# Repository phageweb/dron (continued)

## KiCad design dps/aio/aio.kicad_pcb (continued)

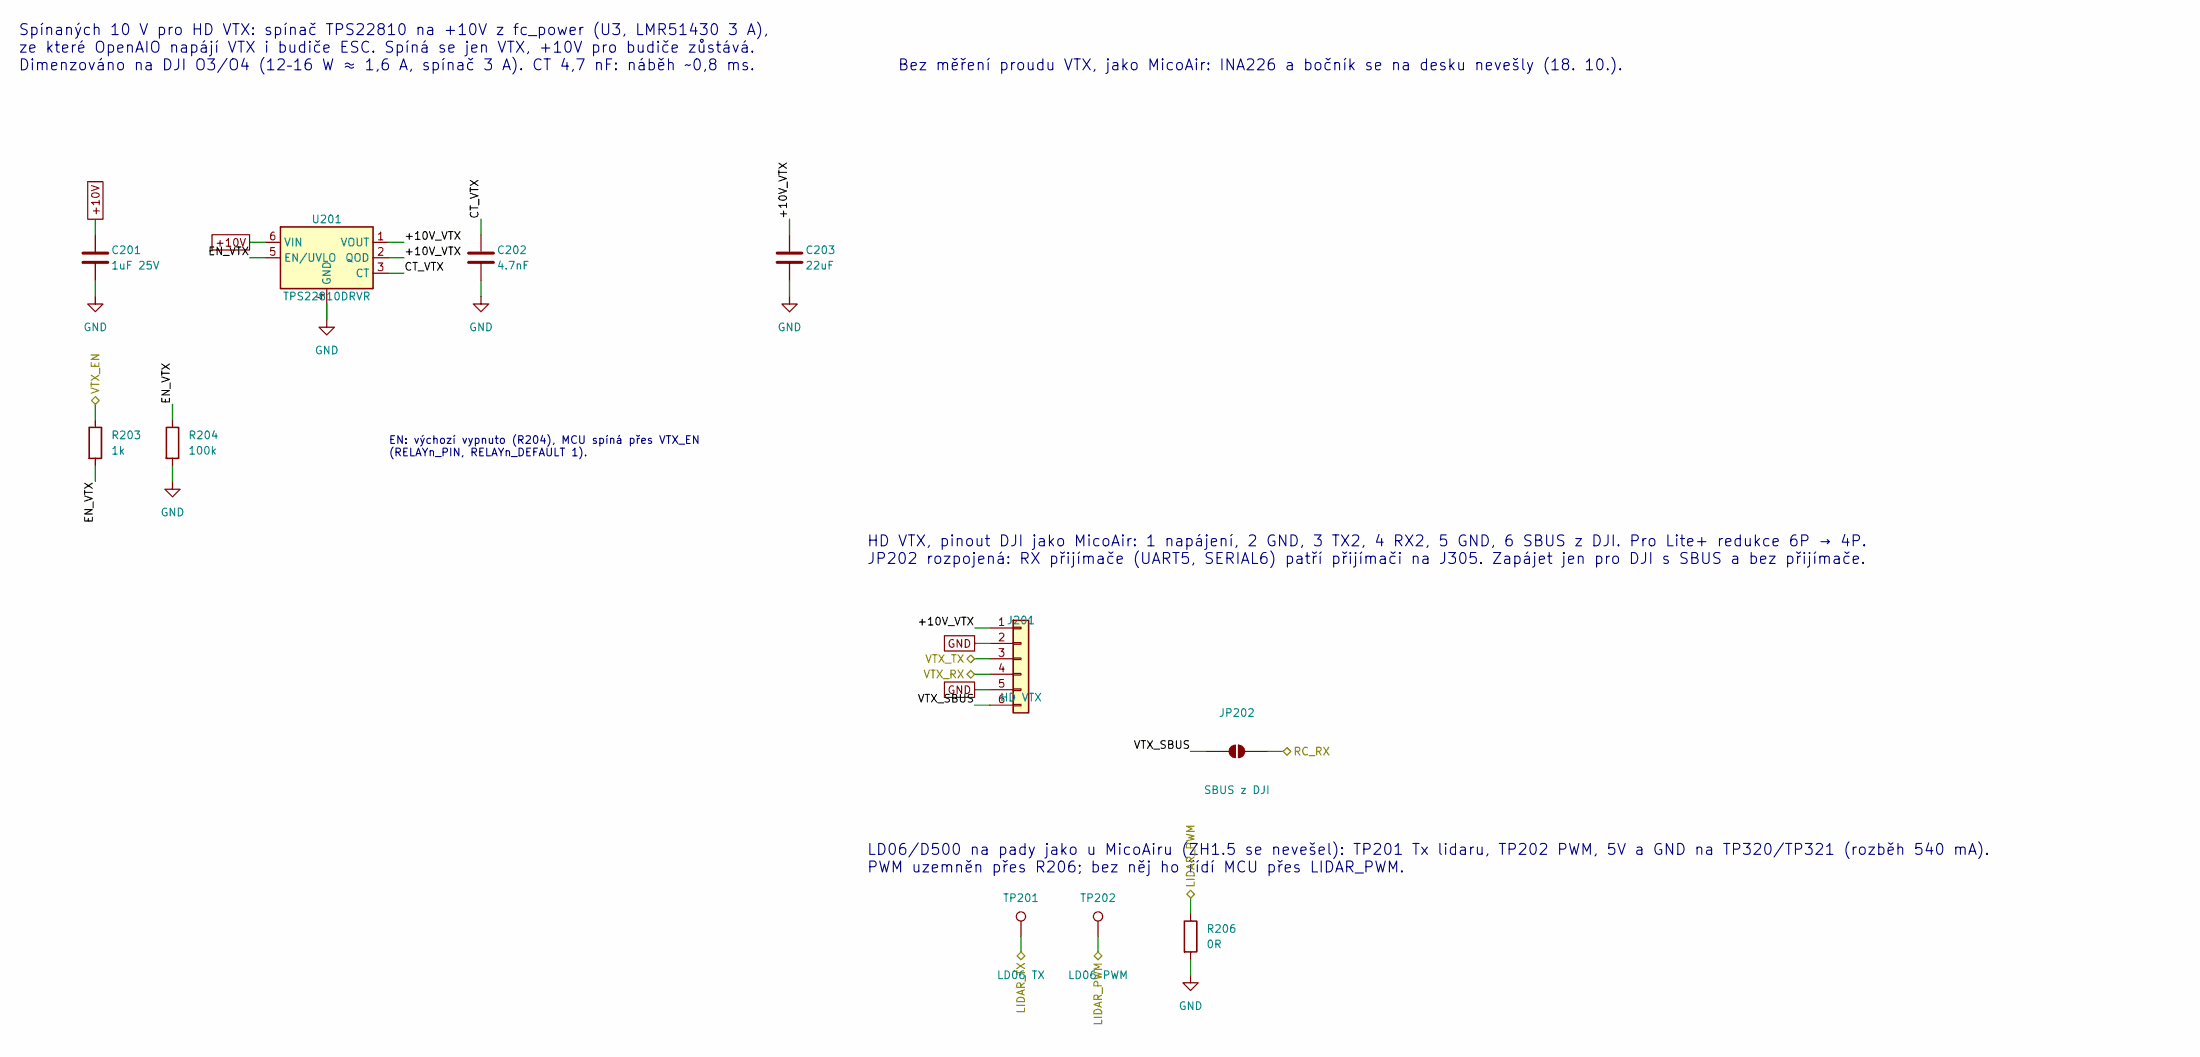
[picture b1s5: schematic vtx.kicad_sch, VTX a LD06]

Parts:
C201: 1uF 25V; C_0402_1005Metric
C202: 4.7nF; C_0201_0603Metric
C203: 22uF; C_0603_1608Metric; LCSC C2762594
J201: HD VTX; JST_SH_SM06B-SRSS-TB_1x06-1MP_P1.00mm_Horizontal; LCSC C160405
JP202: SBUS z DJI; SolderJumper-2_P1.3mm_Open_Pad1.0x1.5mm
R203: 1k; R_0201_0603Metric
R204: 100k; R_0201_0603Metric; LCSC C270364
R206: 0R; R_0201_0603Metric
TP201: LD06 TX; Pad_1.0x1.4mm
TP202: LD06 PWM; Pad_1.0x1.4mm
U201: TPS22810DRVR; WSON-6-1EP_2x2mm_P0.65mm_EP1x1.6mm

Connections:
+10V: C201.1, U201.6 (VIN); also elsewhere on the board
/LIDAR_PWM: R206.1, TP202.1; also elsewhere on the board
/LIDAR_TX: TP201.1; also elsewhere on the board
/RC_RX: JP202.2 (B); also elsewhere on the board
/VTX a LD06/+10V_VTX: C203.1, J201.1, U201.1 (VOUT), U201.2 (QOD)
/VTX a LD06/CT_VTX: C202.1, U201.3 (CT)
/VTX a LD06/EN_VTX: R203.2, R204.1, U201.5 (EN/UVLO)
/VTX a LD06/VTX_SBUS: J201.6, JP202.1 (A)
/VTX_EN: R203.1; also elsewhere on the board
/VTX_RX: J201.4; also elsewhere on the board
/VTX_TX: J201.3; also elsewhere on the board
GND: C201.2, C202.2, C203.2, J201.2, J201.5, R204.2, R206.2, U201.4 (GND), U201.7 (GND); also elsewhere on the board

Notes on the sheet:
Spínaných 10 V pro HD VTX: spínač TPS22810 na +10V z fc_power (U3, LMR51430 3 A), ze které OpenAIO napájí VTX i budiče ESC. Spíná se jen VTX, +10V pro budiče zůstává. Dimenzováno na DJI O3/O4 (12–16 W ≈ 1,6 A, spínač 3 A). CT 4,7 nF: náběh ~0,8 ms.
EN: výchozí vypnuto (R204), MCU spíná přes VTX_EN (RELAYn_PIN, RELAYn_DEFAULT 1).
Bez měření proudu VTX, jako MicoAir: INA226 a bočník se na desku nevešly (18. 10.).
HD VTX, pinout DJI jako MicoAir: 1 napájení, 2 GND, 3 TX2, 4 RX2, 5 GND, 6 SBUS z DJI. Pro Lite+ redukce 6P → 4P. JP202 rozpojená: RX přijímače (UART5, SERIAL6) patří přijímači na J305. Zapájet jen pro DJI s SBUS a bez přijímače.
LD06/D500 na pady jako u MicoAiru (ZH1.5 se nevešel): TP201 Tx lidaru, TP202 PWM, 5V a GND na TP320/TP321 (rozběh 540 mA). PWM uzemněn přes R206; bez něj ho řídí MCU přes LIDAR_PWM.

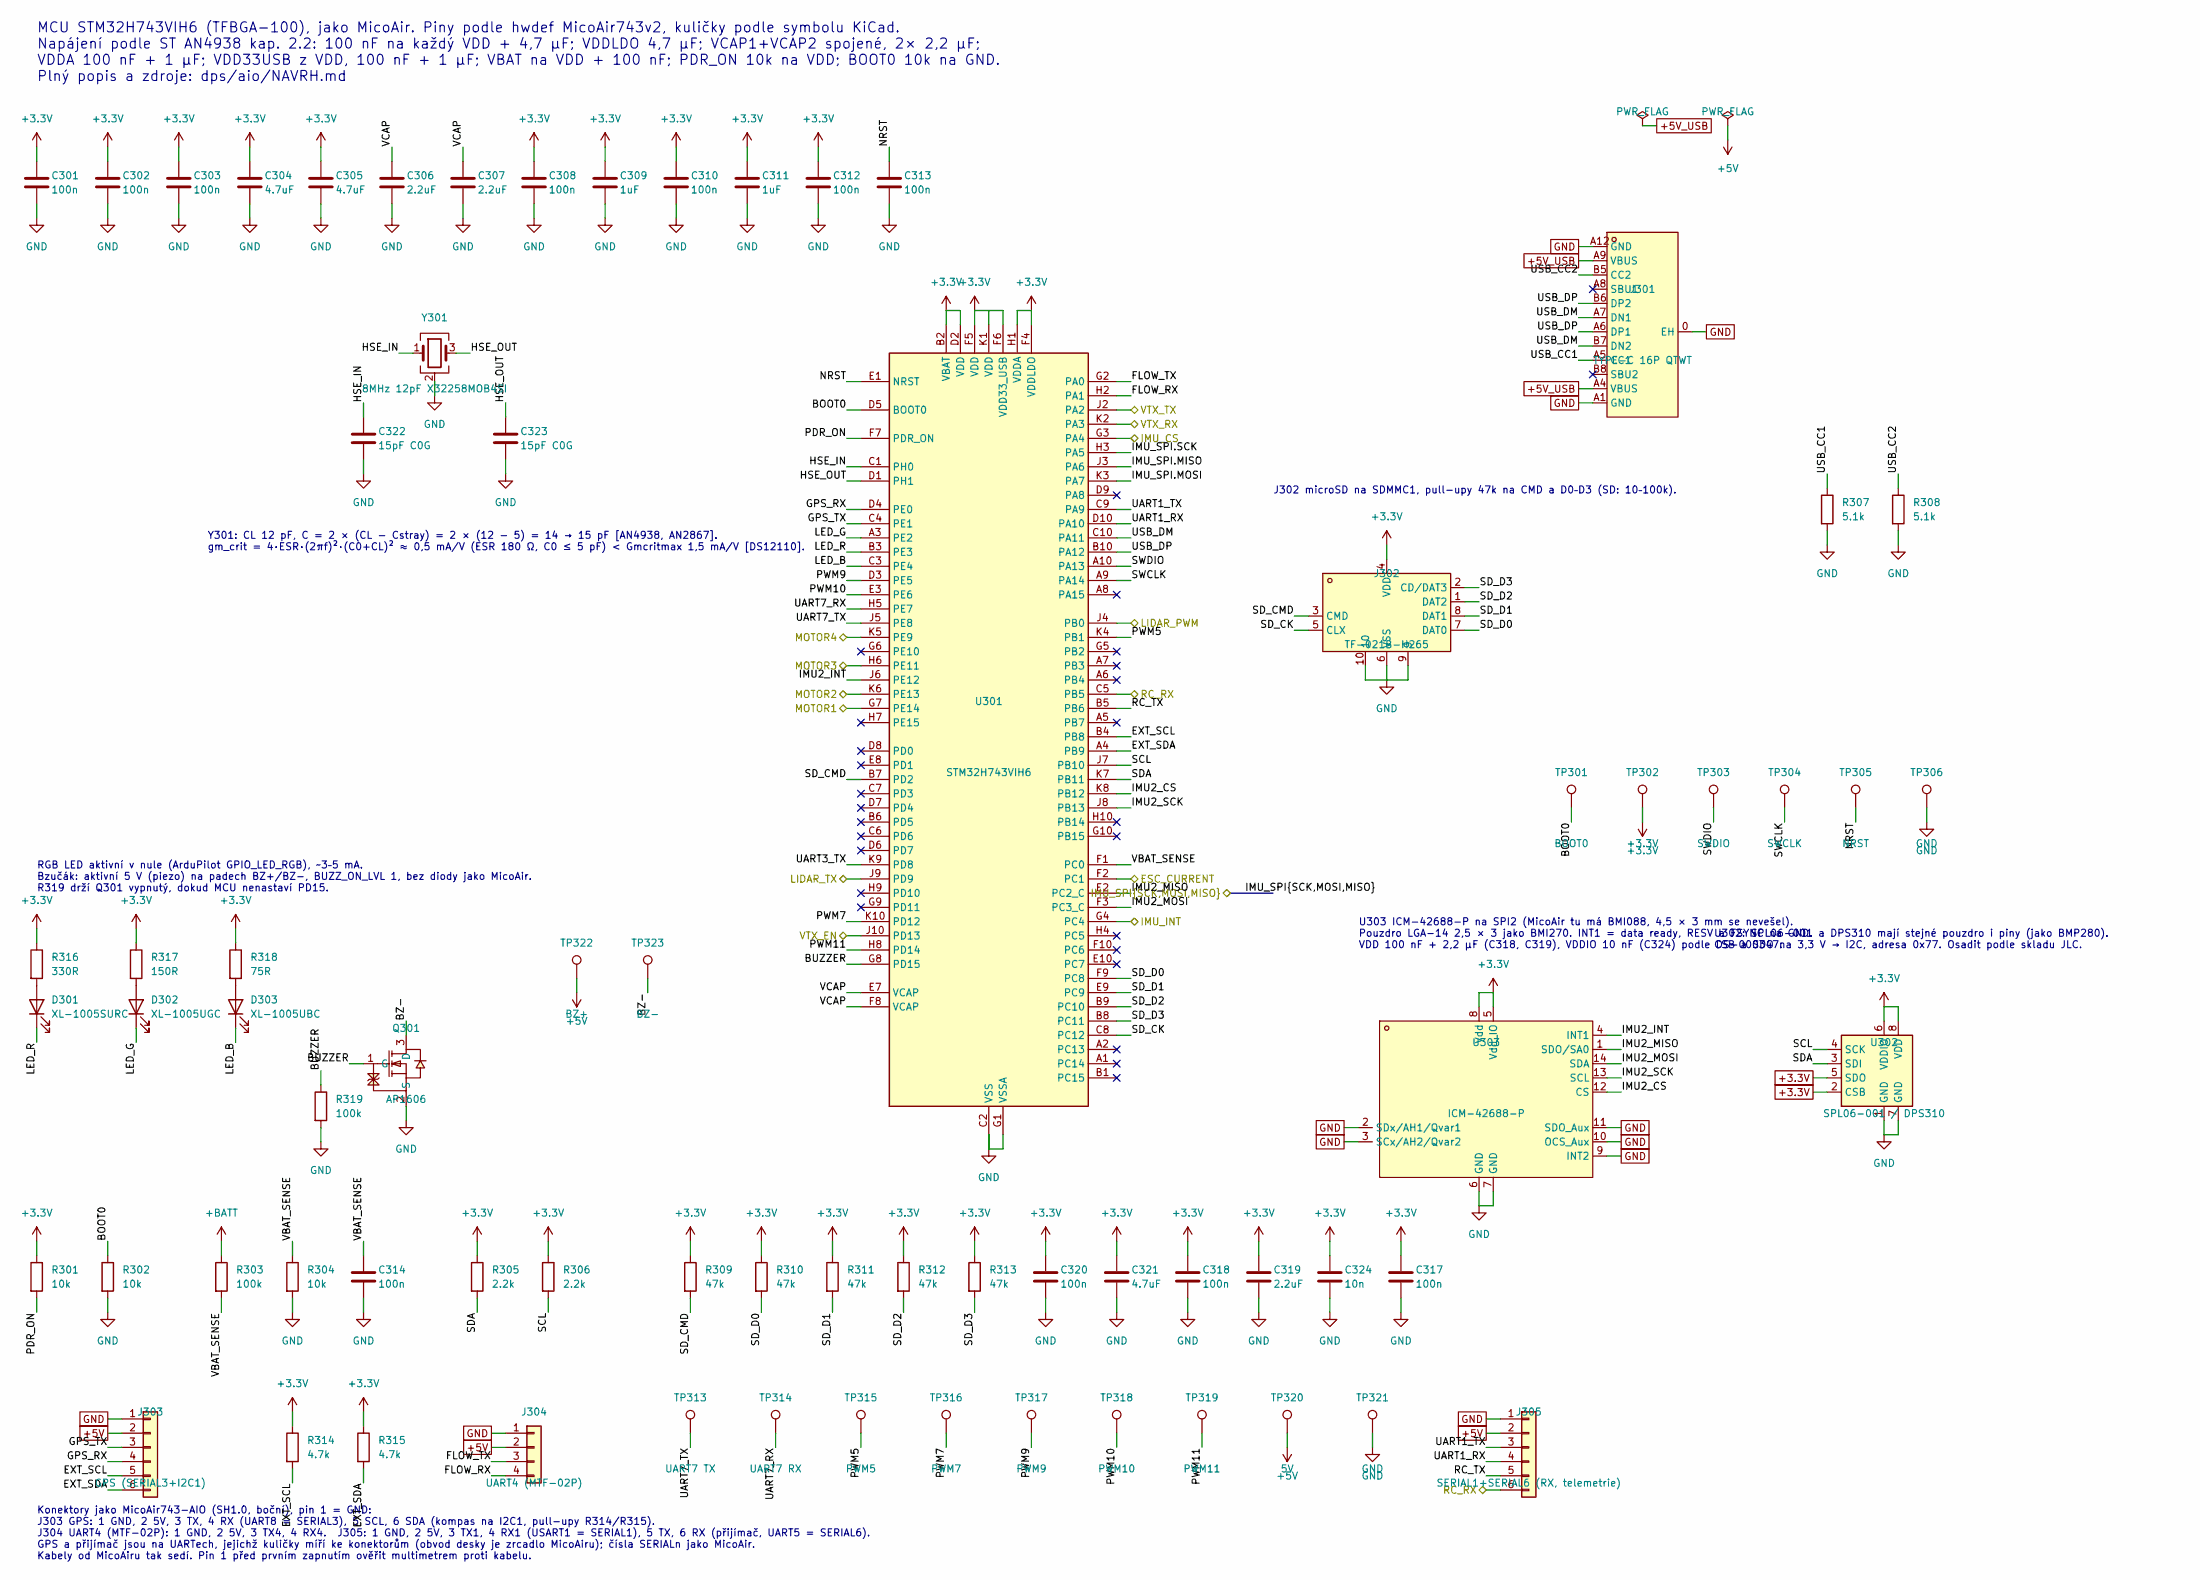
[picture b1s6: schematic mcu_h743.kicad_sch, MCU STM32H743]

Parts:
C301, C302, C303, C308, C310, C312, C313, C314, C317, C318, C320: 100n; C_0201_0603Metric; LCSC C76939
C304, C305, C321: 4.7uF; C_0402_1005Metric; LCSC C23733
C306, C307: 2.2uF; C_0402_1005Metric
C309, C311: 1uF; C_0402_1005Metric
C319: 2.2uF; C_0201_0603Metric
C322, C323: 15pF C0G; C_0402_1005Metric
C324: 10n; C_0201_0603Metric
D301: XL-1005SURC; LED_0402_1005Metric; LCSC C965790
D302: XL-1005UGC; LED_0402_1005Metric; LCSC C965793
D303: XL-1005UBC; LED_0402_1005Metric; LCSC C22355736
J301: TYPE-C 16P QTWT; USB-TYPE-C-SMD_TYPE-C-16P-QTWT; LCSC C5187472
J302: TF-021B-H265; TF-SMD_TF-021B-H265; LCSC C498185
J303: GPS (SERIAL3+I2C1); JST_SH_SM06B-SRSS-TB_1x06-1MP_P1.00mm_Horizontal; LCSC C160405
J304: UART4 (MTF-02P); JST_SH_SM04B-SRSS-TB_1x04-1MP_P1.00mm_Horizontal
J305: SERIAL1+SERIAL6 (RX, telemetrie); JST_SH_SM06B-SRSS-TB_1x06-1MP_P1.00mm_Horizontal; LCSC C160405
Q301: AP1606; DFN-3L_L1.0-W0.6-P0.65-BR; LCSC C2849580
R301, R302, R304: 10k; R_0201_0603Metric
R303, R319: 100k; R_0201_0603Metric; LCSC C270364
R305, R306: 2.2k; R_0201_0603Metric
R307, R308: 5.1k; R_0201_0603Metric; LCSC C270344
R309, R310, R311, R312, R313: 47k; R_0201_0603Metric
R314, R315: 4.7k; R_0201_0603Metric
R316: 330R; R_0201_0603Metric
R317: 150R; R_0201_0603Metric
R318: 75R; R_0201_0603Metric
TP301: BOOT0; Pad_1.0x1.4mm
TP302: +3.3V; Pad_1.0x1.4mm
TP303: SWDIO; Pad_1.0x1.4mm
TP304: SWCLK; Pad_1.0x1.4mm
TP305: NRST; Pad_1.0x1.4mm
TP306, TP321: GND; Pad_1.0x1.4mm
TP313: UART7 TX; Pad_1.0x1.4mm
TP314: UART7 RX; Pad_1.0x1.4mm
TP315: PWM5; Pad_1.0x1.4mm
TP316: PWM7; Pad_1.0x1.4mm
TP317: PWM9; Pad_1.0x1.4mm
TP318: PWM10; Pad_1.0x1.4mm
TP319: PWM11; Pad_1.0x1.4mm
TP320: 5V; Pad_1.0x1.4mm
TP322: BZ+; Pad_1.0x1.4mm
TP323: BZ-; Pad_1.0x1.4mm
U301: STM32H743VIH6; TFBGA-100_8x8mm_Layout10x10_P0.8mm
U302: SPL06-001 / DPS310; Bosch_LGA-8_2x2.5mm_P0.65mm_ClockwisePinNumbering; LCSC C2684428
U303: ICM-42688-P; LGA-14_L3.0-W2.5-P0.50-BR
Y301: 8MHz 12pF X32258MOB4SI; Crystal_SMD_3225-4Pin_3.2x2.5mm; LCSC C2682775

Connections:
+3.3V: C301.1, C302.1, C303.1, C304.1, C305.1, C308.1, C309.1, C310.1, C311.1, C312.1, C317.1, C318.1, C319.1, C320.1, C321.1, C324.1, J302.4 (VDD), R301.1, R305.1, R306.1, R309.1, R310.1, R311.1, R312.1, R313.1, R314.1, R315.1, R316.1, R317.1, R318.1, TP302.1, U301.B2 (VBAT), U301.D2 (VDD), U301.F4 (VDDLDO), U301.F5 (VDD), U301.F6 (VDD33_USB), U301.H1 (VDDA), U301.K1 (VDD), U302.2 (CSB), U302.5 (SDO), U302.6 (VDDIO), U302.8 (VDD), U303.5 (Vdd_IO), U303.8 (Vdd); also elsewhere on the board
+5V: J303.2, J304.2, J305.2, TP320.1, TP322.1; also elsewhere on the board
+5V_USB: J301.A4 (VBUS), J301.A9 (VBUS); also elsewhere on the board
+BATT: R303.1; also elsewhere on the board
/ESC_CURRENT: U301.F2 (PC1); also elsewhere on the board
/IMU_CS: U301.G3 (PA4); also elsewhere on the board
/IMU_INT: U301.G4 (PC4); also elsewhere on the board
/IMU_SPI.MISO: U301.J3 (PA6); also elsewhere on the board
/IMU_SPI.MOSI: U301.K3 (PA7); also elsewhere on the board
/IMU_SPI.SCK: U301.H3 (PA5); also elsewhere on the board
/LIDAR_PWM: U301.J4 (PB0); also elsewhere on the board
/LIDAR_TX: U301.J9 (PD9); also elsewhere on the board
/MCU H743/BOOT0: R302.1, TP301.1, U301.D5 (BOOT0)
/MCU H743/BUZZER: Q301.1 (G), R319.1, U301.G8 (PD15)
/MCU H743/BZ-: Q301.3 (D), TP323.1
/MCU H743/EXT_SCL: J303.5, R314.2, U301.B4 (PB8)
/MCU H743/EXT_SDA: J303.6, R315.2, U301.A4 (PB9)
/MCU H743/FLOW_RX: J304.4, U301.H2 (PA1)
/MCU H743/FLOW_TX: J304.3, U301.G2 (PA0)
/MCU H743/GPS_RX: J303.4, U301.D4 (PE0)
/MCU H743/GPS_TX: J303.3, U301.C4 (PE1)
/MCU H743/HSE_IN: C322.1, U301.C1 (PH0), Y301.1
/MCU H743/HSE_OUT: C323.1, U301.D1 (PH1), Y301.3
/MCU H743/IMU2_CS: U301.K8 (PB12), U303.12 (CS)
/MCU H743/IMU2_INT: U301.J6 (PE12), U303.4 (INT1)
/MCU H743/IMU2_MISO: U301.E2 (PC2_C), U303.1 (SDO/SA0)
/MCU H743/IMU2_MOSI: U301.F3 (PC3_C), U303.14 (SDA)
/MCU H743/IMU2_SCK: U301.J8 (PB13), U303.13 (SCL)
/MCU H743/LED_B: D303.1 (K), U301.C3 (PE4)
/MCU H743/LED_G: D302.1 (K), U301.A3 (PE2)
/MCU H743/LED_R: D301.1 (K), U301.B3 (PE3)
/MCU H743/NRST: C313.1, TP305.1, U301.E1 (NRST)
/MCU H743/PDR_ON: R301.2, U301.F7 (PDR_ON)
/MCU H743/PWM5: TP315.1, U301.K4 (PB1)
/MCU H743/PWM7: TP316.1, U301.K10 (PD12)
/MCU H743/PWM9: TP317.1, U301.D3 (PE5)
/MCU H743/PWM10: TP318.1, U301.E3 (PE6)
/MCU H743/PWM11: TP319.1, U301.H8 (PD14)
/MCU H743/RC_TX: J305.5, U301.B5 (PB6)
/MCU H743/SCL: R306.2, U301.J7 (PB10), U302.4 (SCK)
/MCU H743/SDA: R305.2, U301.K7 (PB11), U302.3 (SDI)
/MCU H743/SD_CK: J302.5 (CLX), U301.C8 (PC12)
/MCU H743/SD_CMD: J302.3 (CMD), R309.2, U301.B7 (PD2)
/MCU H743/SD_D0: J302.7 (DAT0), R310.2, U301.F9 (PC8)
/MCU H743/SD_D1: J302.8 (DAT1), R311.2, U301.E9 (PC9)
/MCU H743/SD_D2: J302.1 (DAT2), R312.2, U301.B9 (PC10)
/MCU H743/SD_D3: J302.2 (CD/DAT3), R313.2, U301.B8 (PC11)
/MCU H743/SWCLK: TP304.1, U301.A9 (PA14)
/MCU H743/SWDIO: TP303.1, U301.A10 (PA13)
/MCU H743/UART1_RX: J305.4, U301.D10 (PA10)
/MCU H743/UART1_TX: J305.3, U301.C9 (PA9)
/MCU H743/UART3_TX: U301.K9 (PD8)
/MCU H743/UART7_RX: TP314.1, U301.H5 (PE7)
/MCU H743/UART7_TX: TP313.1, U301.J5 (PE8)
/MCU H743/USB_CC1: J301.A5 (CC1), R307.1
/MCU H743/USB_CC2: J301.B5 (CC2), R308.1
/MCU H743/USB_DM: J301.A7 (DN1), J301.B7 (DN2), U301.C10 (PA11)
/MCU H743/USB_DP: J301.A6 (DP1), J301.B6 (DP2), U301.B10 (PA12)
/MCU H743/VBAT_SENSE: C314.1, R303.2, R304.1, U301.F1 (PC0)
/MCU H743/VCAP: C306.1, C307.1, U301.E7 (VCAP), U301.F8 (VCAP)
/MOTOR1: U301.G7 (PE14); also elsewhere on the board
/MOTOR2: U301.K6 (PE13); also elsewhere on the board
/MOTOR3: U301.H6 (PE11); also elsewhere on the board
/MOTOR4: U301.K5 (PE9); also elsewhere on the board
/RC_RX: J305.6, U301.C5 (PB5); also elsewhere on the board
/VTX_EN: U301.J10 (PD13); also elsewhere on the board
/VTX_RX: U301.K2 (PA3); also elsewhere on the board
/VTX_TX: U301.J2 (PA2); also elsewhere on the board
GND: C301.2, C302.2, C303.2, C304.2, C305.2, C306.2, C307.2, C308.2, C309.2, C310.2, C311.2, C312.2, C313.2, C314.2, C317.2, C318.2, C319.2, C320.2, C321.2, C322.2, C323.2, C324.2, J301.0 (EH), J301.A1 (GND), J301.A12 (GND), J302.6 (VSS), J302.9, J302.10, J303.1, J304.1, J305.1, Q301.2 (S), R302.2, R304.2, R307.2, R308.2, R319.2, TP306.1, TP321.1, U301.C2 (VSS), U301.E4 (VSS), U301.E5 (VSS), U301.E6 (VSS), U301.G1 (VSSA), U301.J1 (VSS), U302.1 (GND), U302.7 (GND), U303.2 (SDx/AH1/Qvar1), U303.3 (SCx/AH2/Qvar2), U303.6 (GND), U303.7 (GND), U303.9 (INT2), U303.10 (OCS_Aux), U303.11 (SDO_Aux), Y301.2 (G), Y301.4 (G); also elsewhere on the board
unnamed: D301.2 (A), R316.2
unnamed: D302.2 (A), R317.2
unnamed: D303.2 (A), R318.2

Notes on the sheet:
MCU STM32H743VIH6 (TFBGA-100), jako MicoAir. Piny podle hwdef MicoAir743v2, kuličky podle symbolu KiCad. Napájení podle ST AN4938 kap. 2.2: 100 nF na každý VDD + 4,7 µF; VDDLDO 4,7 µF; VCAP1+VCAP2 spojené, 2× 2,2 µF; VDDA 100 nF + 1 µF; VDD33USB z VDD, 100 nF + 1 µF; VBAT na VDD + 100 nF; PDR_ON 10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
RGB LED aktivní v nule (ArduPilot GPIO_LED_RGB), ~3–5 mA. Bzučák: aktivní 5 V (piezo) na padech BZ+/BZ−, BUZZ_ON_LVL 1, bez diody jako MicoAir. R319 drží Q301 vypnutý, dokud MCU nenastaví PD15.
Y301: CL 12 pF, C = 2 × (CL − Cstray) = 2 × (12 − 5) = 14 → 15 pF [AN4938, AN2867]. gm_crit = 4·ESR·(2πf)²·(C0+CL)² ≈ 0,5 mA/V (ESR 180 Ω, C0 ≤ 5 pF) < Gmcritmax 1,5 mA/V [DS12110].
U302: SPL06-001 a DPS310 mají stejné pouzdro i piny (jako BMP280). CSB a SDO na 3,3 V → I2C, adresa 0x77. Osadit podle skladu JLC.
U303 ICM-42688-P na SPI2 (MicoAir tu má BMI088, 4,5 × 3 mm se nevešel). Pouzdro LGA-14 2,5 × 3 jako BMI270. INT1 = data ready, RESV a FSYNC na GND. VDD 100 nF + 2,2 µF (C318, C319), VDDIO 10 nF (C324) podle DS-000347.
J302 microSD na SDMMC1, pull-upy 47k na CMD a D0–D3 (SD: 10–100k).
Konektory jako MicoAir743-AIO (SH1.0, boční), pin 1 = GND: J303 GPS: 1 GND, 2 5V, 3 TX, 4 RX (UART8 = SERIAL3), 5 SCL, 6 SDA (kompas na I2C1, pull-upy R314/R315). J304 UART4 (MTF-02P): 1 GND, 2 5V, 3 TX4, 4 RX4. J305: 1 GND, 2 5V, 3 TX1, 4 RX1 (USART1 = SERIAL1), 5 TX, 6 RX (přijímač, UART5 = SERIA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

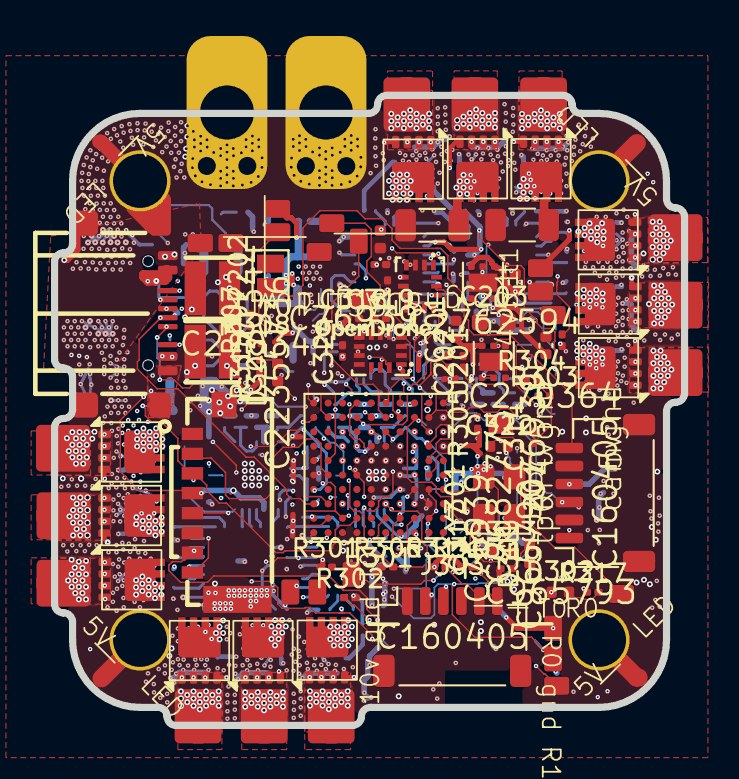
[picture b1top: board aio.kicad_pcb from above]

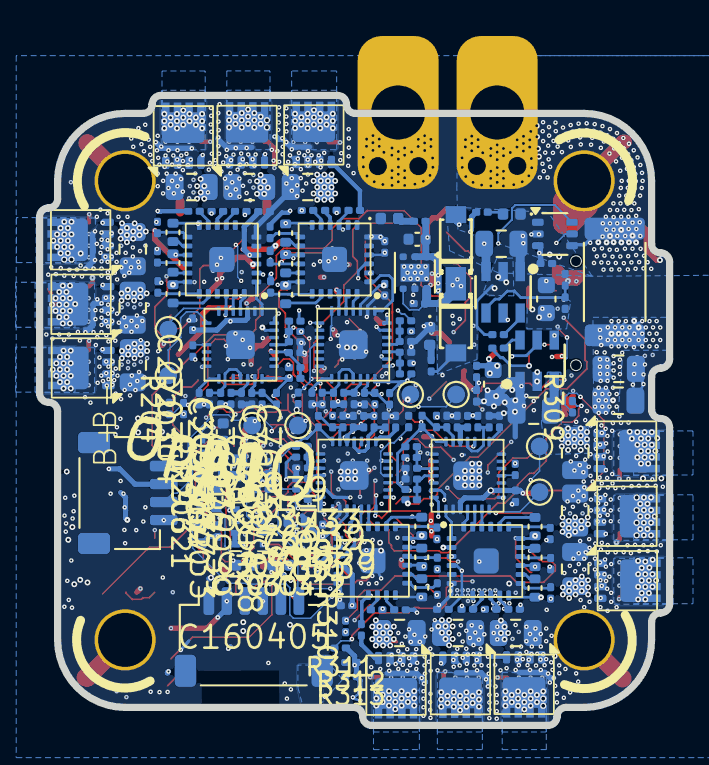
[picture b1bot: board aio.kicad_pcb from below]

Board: 8 copper layers, 35.0 x 35.0 mm, 280 parts (200 on the bottom side), 225 nets.

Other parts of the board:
R54, R74: 15R; R_0201_0603Metric
R59: 10R; R_0201_0603Metric
R76: 10k; R_0201_0603Metric

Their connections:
+3.3V: R59.2; also elsewhere on the board
/ESC2/GHA: R54.1; also elsewhere on the board
/ESC2/vdda: R59.1; also elsewhere on the board
/ESC3/GLA: R74.1; also elsewhere on the board
GND: R76.2; also elsewhere on the board
unnamed 171: R54.2; also elsewhere on the board
unnamed 178: R74.2; also elsewhere on the board
unnamed 211: R76.1; also elsewhere on the board

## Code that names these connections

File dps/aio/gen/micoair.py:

"""MicoAir743v2-AIO-45A reference; deliberately not the older 35 A AIO.

Pinout: https://micoair.com/flightcontroller_micoair743v2_aio_45a/
Firmware: external/ardupilot/.../hwdef/MicoAir743v2/hwdef.dat (pinned locally).
This is a functional reference, not a reconstruction of its undocumented copper.
"""
import re

# Logical board signal -> MCU GPIO. ICM42688 takes the BMI088 accelerometer's
# SPI2 CS/DRDY; this is our adaptation, not a claim about MicoAir's fitted IMU.
PINS = {
    "MOTOR1": "PE14", "MOTOR2": "PE13", "MOTOR3": "PE11", "MOTOR4": "PE9",
    "IMU_SPI.SCK": "PB3", "IMU_SPI.MISO": "PB4", "IMU_SPI.MOSI": "PD6",
    "IMU_CS": "PA15", "IMU_INT": "PB7",
    "IMU2_SCK": "PD3", "IMU2_MISO": "PC2", "IMU2_MOSI": "PC3",
    "IMU2_CS": "PD4", "IMU2_INT": "PC14",
    "GPS_TX": "PD8", "GPS_RX": "PD9", "RC_TX": "PC6", "RC_RX": "PC7",
    "LIDAR_TX": "PB5", "UART5_TX": "PB6", "UART8_TX": "PE1", "UART8_RX": "PE0",
    "UART1_TX": "PA9", "UART1_RX": "PA10", "VTX_TX": "PA2", "VTX_RX": "PA3",
    "FLOW_TX": "PA0", "FLOW_RX": "PA1", "EXT_SCL": "PB8", "EXT_SDA": "PB9",
    "SCL": "PB10", "SDA": "PB11", "VBAT_SENSE": "PC0", "ESC_CURRENT": "PC1",
    "USB_DM": "PA11", "USB_DP": "PA12", "SWDIO": "PA13", "SWCLK": "PA14",
    "SD_CK": "PC12", "SD_CMD": "PD2", "SD_D0": "PC8", "SD_D1": "PC9",
    "SD_D2": "PC10", "SD_D3": "PC11", "LED_R": "PE3", "LED_G": "PE2", "LED_B": "PE4",
    "BUZZER": "PD15", "PWM5": "PB1", "LIDAR_PWM": "PB0", "PWM7": "PD12",
    "VTX_EN": "PD13", "PWM9": "PE5", "PWM10": "PE6", "PWM11": "PD14",
}
ALIASES = {"UART3_TX": "UART5_TX", "UART7_TX": "UART8_TX", "UART7_RX": "UART8_RX"}
SERIAL_ORDER = "OTG1 USART1 USART2 USART3 UART4 UART5 USART6 UART7 UART8"


def gpio(name):
    """KiCad calls the analog-switch pins PC2_C/PC3_C; hwdef calls them PC2/PC3."""
    match = re.match(r"P[A-K]\d+", name)
    return match.group() if match else name


def remap(balls, pin_names):
    by_pin = {gpio(name): ball for ball, name in pin_names.items()}
    out = {ball: net for ball, net in balls.items() if ALIASES.get(net, net) not in PINS}
    for net, pin in PINS.items():
        ball = by_pin[pin]
        if ball in out and out[ball] is not None:
            raise ValueError(f"{net}/{pin} would replace {out[ball]} at {ball}")
        out[ball] = net
    return out


def hwdef(text):
    """Render the reference variant from our board's hwdef, keeping its electrical calibration."""
    text = re.sub(r"SERIAL_ORDER[^\n]*", "SERIAL_ORDER  " + SERIAL_ORDER, text)
    start, end = text.index("# order of UARTs"), text.index("# SWD")
    uarts = "\n".join(f"{pin:4} {bus}_{direction:2} {bus}" for bus, tx, rx in (
        ("USART1", "PA9", "PA10"), ("USART2", "PA2", "PA3"), ("USART3", "PD8", "PD9"),
        ("UART4", "PA0", "PA1"), ("UART5", "PB6", "PB5"), ("USART6", "PC6", "PC7"),
        ("UART7", "PE8", "PE7"), ("UART8", "PE1", "PE0"))
        for pin, direction in ((tx, "TX"), (rx, "RX")))
    text = text[:start] + ("# UART order/pins follow MicoAir743v2-AIO-45A.\n"
        "# SERIAL3 GPS; SERIAL5 LD06; SERIAL6 RC; SERIAL8 Bluetooth pads.\n"
        "SERIAL_ORDER  " + SERIAL_ORDER + "\n\nPA11 OTG_FS_DM OTG1\nPA12 OTG_FS_DP OTG1\n\n"
        + uarts + "\n\n") + text[end:]
    start, end = text.index("# SPI2 -"), text.index("# IMUs:")
    text = text[:start] + """# SPI2: our ICM42688 on the reference BMI088 accel CS/DRDY pins.
PD3 SPI2_SCK SPI2
PC2 SPI2_MISO SPI2
PC3 SPI2_MOSI SPI2
PD4 ICM42688_CS CS
PC14 DRDY1_ICM42688 INPUT

# SPI3: BMI270, same pins as MicoAir743v2-AIO-45A.
PB3 SPI3_SCK SPI3
PB4 SPI3_MISO SPI3
PD6 SPI3_MOSI SPI3
PA15 BMI270_CS CS
PB7 DRDY3_BMI270 INPUT

SPIDEV icm42688 SPI2 DEVID1 ICM42688_CS MODE3 2*MHZ 16*MHZ
SPIDEV bmi270 SPI3 DEVID1 BMI270_CS MODE3 1*MHZ 10*MHZ

""" + text[end:]
    return "# Generated reference variant by gen/micoair.py; verify IMU rotations after placement.\n" + text

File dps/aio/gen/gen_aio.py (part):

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v.part("JP202", "Jumper:SolderJumper_2_Open", "SBUS z DJI", "Jumper:SolderJumper-2_P1.3mm_Open_Pad1.0x1.5mm", "",
       238.76, 132.08, {"1": "VTX_SBUS", "2": "RC_RX"})
v.text("Spínaných 10 V pro HD VTX: spínač TPS22810 na +10V z fc_power (U3, LMR51430 3 A),\nze které OpenAIO napájí VTX i budiče ESC. Spíná se jen VTX, +10V pro budiče zůstává.\nDimenzováno na DJI O3/O4 (12–16 W ≈ 1,6 A, spínač 3 A). CT 4,7 nF: náběh ~0,8 ms.", 38.1, 20.32, 1.8)
v.text("EN: výchozí vypnuto (R204), MCU spíná přes VTX_EN\n(RELAYn_PIN, RELAYn_DEFAULT 1).", 99.06, 83.82)
v.text("Bez měření proudu VTX, jako MicoAir: INA226 a bočník se na desku nevešly (18. 10.).", 182.88, 20.32, 1.8)
v.text("HD VTX, pinout DJI jako MicoAir: 1 napájení, 2 GND, 3 TX2, 4 RX2, 5 GND, 6 SBUS z DJI. Pro Lite+ redukce 6P → 4P.\nJP202 rozpojená: RX přijímače (UART5, SERIAL6) patří přijímači na J305. Zapájet jen pro DJI s SBUS a bez přijímače.", 177.8, 101.6, 1.8)
v.text("LD06/D500 na pady jako u MicoAiru (ZH1.5 se nevešel): TP201 Tx lidaru, TP202 PWM, 5V a GND na TP320/TP321 (rozběh 540 mA).\nPWM uzemněn přes R206; bez něj ho řídí MCU přes LIDAR_PWM.", 177.8, 152.4, 1.8)
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    "C1": "HSE_IN", "D1": "HSE_OUT",
    # hwdef MicoAir743v2, except three UARTs (19. 10.): our board's edge is MicoAir's mirrored, so GPS and the
    # receiver take the UARTs whose balls face the connectors (bottom edge); SERIAL_ORDER keeps MicoAir's numbers
    "G7": "MOTOR1", "K6": "MOTOR2", "H6": "MOTOR3", "K5": "MOTOR4",            # PE14 PE13 PE11 PE9, TIM1
    # both IMUs sit above the BGA (19. 10.): BMI270 on SPI1 (free, MicoAir's OSD) instead of SPI3, whose
    # balls face down; the ICM's SCK, CS and DRDY on balls of the top rows
    "H3": "IMU_SPI.SCK", "K3": "IMU_SPI.MOSI", "J3": "IMU_SPI.MISO",           # PA5 PA7 PA6, SPI1
    "G3": "IMU_CS", "G4": "IMU_INT",                                          # PA4 PC4, BMI270
    "J8": "IMU2_SCK", "E2": "IMU2_MISO", "F3": "IMU2_MOSI",                   # PB13 PC2_C PC3_C, SPI2
    "K8": "IMU2_CS", "J6": "IMU2_INT",                                       # PB12 PE12, ICM-42688-P
    "F1": "VBAT_SENSE", "F2": "ESC_CURRENT",                                  # PC0 PC1, ADC1
    "K7": "SDA", "J7": "SCL",                                                 # PB11 PB10, I2C2 = bus 0
    "A4": "EXT_SDA", "B4": "EXT_SCL",                                         # PB9 PB8, I2C1 = bus 1
    "C9": "UART1_TX", "D10": "UART1_RX",                                      # PA9 PA10, SERIAL1
    "J2": "VTX_TX", "K2": "VTX_RX",                                           # PA2 PA3, USART2 = SERIAL2
    "C4": "GPS_TX", "D4": "GPS_RX",                                           # PE1 PE0, UART8 = SERIAL3
    "G2": "FLOW_TX", "H2": "FLOW_RX",                                         # PA0 PA1, UART4 = SERIAL4
    "K9": "UART3_TX", "J9": "LIDAR_TX",                                       # PD8 PD9, USART3 = SERIAL5
    "B5": "RC_TX", "C5": "RC_RX",                                             # PB6 PB5, UART5 = SERIAL6
    "J5": "UART7_TX", "H5": "UART7_RX",                                       # PE8 PE7, SERIAL8
    "C10": "USB_DM", "B10": "USB_DP",                                         # PA11 PA12, OTG_FS
    "A10": "SWDIO", "A9": "SWCLK",                                            # PA13 PA14
    "C8": "SD_CK", "B7": "SD_CMD", "F9": "SD_D0", "E9": "SD_D1", "B9": "SD_D2", "B8": "SD_D3",  # SDMMC1
    "B3": "LED_R", "A3": "LED_G", "C3": "LED_B", "G8": "BUZZER",              # PE3 PE2 PE4 PD15
    "J4": "LIDAR_PWM", "J10": "VTX_EN",                                       # PB0 = PWM6, PD13 = PWM8
    "K4": "PWM5", "K10": "PWM7", "D3": "PWM9", "E3": "PWM10", "H8": "PWM11",  # PB1 PD12 PE5 PE6 PD14
}
_balls = pins_of(LIB["MCU_ST_STM32H7:STM32H743VIHx"])
if MICOAIR:
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m.part("TP323", "lib:TestPoint", "BZ-", TP, "", 139.7, 182.88, {"1": "BZ-"})
m.text("""RGB LED aktivní v nule (ArduPilot GPIO_LED_RGB), ~3–5 mA.
Bzučák: aktivní 5 V (piezo) na padech BZ+/BZ−, BUZZ_ON_LVL 1, bez diody jako MicoAir.
R319 drží Q301 vypnutý, dokud MCU nenastaví PD15.""", 30.48, 167.64, 1.27)
m.text("""Y301: CL 12 pF, C = 2 × (CL − Cstray) = 2 × (12 − 5) = 14 → 15 pF [AN4938, AN2867].
gm_crit = 4·ESR·(2πf)²·(C0+CL)² ≈ 0,5 mA/V (ESR 180 Ω, C0 ≤ 5 pF) < Gmcritmax 1,5 mA/V [DS12110].""", 60.96, 106.68, 1.27)
m.text("""U302: SPL06-001 a DPS310 mají stejné pouzdro i piny (jako BMP280).
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J304 UART4 (MTF-02P): 1 GND, 2 5V, 3 TX4, 4 RX4.  J305: 1 GND, 2 5V, 3 TX1, 4 RX1 (USART1 = SERIAL1), 5 TX, 6 RX (přijímač, UART5 = SERIAL6).
GPS a přijímač jsou na UARTech, jejichž kuličky míří ke konektorům (obvod desky je zrcadlo MicoAiru); čísla SERIALn jako MicoAir.
Kabely od MicoAiru tak sedí. Pin 1 před prvním zapnutím ověřit multimetrem proti kabelu.""" if not MICOAIR else
"""Reference MicoAir743v2-AIO-45A: J303 GPS USART3 (PD8/PD9), J305 RC USART6 (PC6/PC7).
LD06 UART5 RX PB5; Bluetooth UART8 PE1/PE0. BMI270 SPI3, ICM42688 SPI2.
Konektory mají náš pinout; orientaci a pin 1 ověřit proti kabelu. Layout této varianty čeká na ověření.""",
       30.48, 287.02, 1.27)
m.place("#FLG301", "power:PWR_FLAG", "PWR_FLAG", "", "", 317.5, 30.48, power=True, ref_at=(317.5, 27), val_at=(317.5, 27.94))
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
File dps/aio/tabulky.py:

#!/usr/bin/env python3
"""Regenerate the tables in NAVRH.md from the schematic.

    nix develop ./dps -c python3 dps/aio/tabulky.py [PROJECT] [--profile current|micoair-v2]

Exports the netlist with kicad-cli and rewrites everything between the
<!-- tabulky:NAME --> and <!-- /tabulky:NAME --> markers in NAVRH.md.
"""
import argparse, collections, os, re, subprocess, tempfile
import xml.etree.ElementTree as ET

parser = argparse.ArgumentParser(description=__doc__)
parser.add_argument("project", nargs="?", default=os.path.dirname(os.path.abspath(__file__)))
parser.add_argument("--profile", choices=("current", "micoair-v2"), default="current")
args = parser.parse_args()
HERE = os.path.abspath(args.project)
DOC = os.path.join(HERE, "NAVRH.md")

# What each H743 signal does in ArduPilot (hwdef Pavo20AIO: MicoAir743v2, IMUs and three UARTs moved) and where it goes.
FUNCTION = {
    "MOTOR1": "PWM1, TIM1_CH4, BIDIR DShot", "MOTOR2": "PWM2, TIM1_CH3", "MOTOR3": "PWM3, TIM1_CH2, BIDIR DShot",
    "MOTOR4": "PWM4, TIM1_CH1", "PWM5": "PWM5, TIM3_CH4, GPIO 54", "LIDAR_PWM": "PWM6, TIM3_CH3, GPIO 55",
    "PWM7": "PWM7, TIM4_CH1, GPIO 56", "VTX_EN": "PWM8 jako GPIO 57 (RELAYn_PIN 57)", "PWM9": "PWM9, TIM15_CH1, GPIO 58",
    "PWM10": "PWM10, TIM15_CH2, GPIO 59", "PWM11": "PWM11, TIM4_CH3, GPIO 60 (LED pad)",
    "IMU_SPI.SCK": "SPI1_SCK", "IMU_SPI.MOSI": "SPI1_MOSI", "IMU_SPI.MISO": "SPI1_MISO", "IMU_CS": "BMI270_CS",
    "IMU_INT": "DRDY3_BMI270", "IMU2_SCK": "SPI2_SCK", "IMU2_MISO": "SPI2_MISO", "IMU2_MOSI": "SPI2_MOSI",
    "IMU2_CS": "ICM42688_CS", "IMU2_INT": "DRDY1_ICM42688", "VBAT_SENSE": "ADC1 ch10, BATT_VOLTAGE_SENS",
    "ESC_CURRENT": "ADC1 ch11, BATT_CURRENT_SENS", "SDA": "I2C2_SDA (bus 0)", "SCL": "I2C2_SCL (bus 0)",
    "EXT_SDA": "I2C1_SDA (bus 1)", "EXT_SCL": "I2C1_SCL (bus 1)", "UART1_TX": "USART1_TX, SERIAL1",
    "UART1_RX": "USART1_RX, SERIAL1", "VTX_TX": "USART2_TX, SERIAL2", "VTX_RX": "USART2_RX, SERIAL2",
    "GPS_TX": "UART8_TX, SERIAL3", "GPS_RX": "UART8_RX, SERIAL3", "FLOW_TX": "UART4_TX, SERIAL4",
    "FLOW_RX": "UART4_RX, SERIAL4", "UART3_TX": "USART3_TX, SERIAL5", "LIDAR_TX": "USART3_RX, SERIAL5",
    "RC_TX": "UART5_TX, SERIAL6", "RC_RX": "UART5_RX, SERIAL6", "UART7_TX": "UART7_TX, SERIAL8",
    "UART7_RX": "UART7_RX, SERIAL8",
    "USB_DM": "OTG_FS_DM, SERIAL0", "USB_DP": "OTG_FS_DP, SERIAL0", "SWDIO": "SWD", "SWCLK": "SWD",
    "SD_CK": "SDMMC1_CK", "SD_CMD": "SDMMC1_CMD", "SD_D0": "SDMMC1_D0", "SD_D1": "SDMMC1_D1",
    "SD_D2": "SDMMC1_D2", "SD_D3": "SDMMC1_D3", "LED_R": "LED_RED, GPIO 0", "LED_G": "LED_GREEN, GPIO 1",
    "LED_B": "LED_BLUE, GPIO 2", "BUZZER": "BUZZER, GPIO 61", "HSE_IN": "OSC_IN, 8 MHz", "HSE_OUT": "OSC_OUT",
    "BOOT0": "BOOT0", "NRST": "reset", "PDR_ON": "napěťový dozor", "VCAP": "výstup LDO jádra",
}
if args.profile == "micoair-v2":
    FUNCTION.update({
        "IMU_SPI.SCK": "SPI3_SCK", "IMU_SPI.MOSI": "SPI3_MOSI", "IMU_SPI.MISO": "SPI3_MISO",
        "GPS_TX": "USART3_TX, SERIAL3", "GPS_RX": "USART3_RX, SERIAL3",
        "RC_TX": "USART6_TX, SERIAL6", "RC_RX": "USART6_RX, SERIAL6",
        "LIDAR_TX": "UART5_RX, SERIAL5", "UART5_TX": "UART5_TX, SERIAL5",
        "UART8_TX": "UART8_TX, SERIAL8", "UART8_RX": "UART8_RX, SERIAL8",
    })


def netlist():
    with tempfile.TemporaryDirectory() as d:
        out = os.path.join(d, "aio.xml")
        subprocess.run(["kicad-cli", "sch", "export", "netlist", "--format", "kicadxml", "-o", out,
                        os.path.join(HERE, "aio.kicad_sch")], check=True, capture_output=True)
        return ET.parse(out).getroot()


def short(net):
    return re.sub(r"^/(?:[^/]+/)*", "", net) if net.startswith("/") else net


def main():
    t = netlist()
    comps = {}
    for c in t.find("components"):
        f = {x.get("name"): x.text or "" for x in c.findall("fields/field")}
        comps[c.get("ref")] = dict(value=c.findtext("value"), fp=(c.findtext("footprint") or "").split(":")[-1],
                                   lcsc=f.get("LCSC", ""), sheet=c.find("sheetpath").get("names"))
    pins = collections.defaultdict(dict)
    nets = collections.defaultdict(list)
    for n in t.find("nets"):
        name = n.get("name")
        for x in n.findall("node"):
            pins[x.get("ref")][x.get("pin")] = (name, x.get("pinfunction") or "")
            nets[name].append(x.get("ref"))

    tables = {}

    # bill of materials, per sheet
    by = collections.defaultdict(list)
    for ref, c in comps.items():
        by[c["sheet"]].append(ref)
    key = lambda r: (re.sub(r"\d+", "", r), int(re.sub(r"\D", "", r) or 0))
    out = []
    for sheet in sorted(by, key=lambda s: (s != "/", s)):
        refs = sorted(by[sheet], key=key)
        out.append(f"\n**{sheet}** ({len(refs)} dílů)\n")
        out.append("| Ref | Hodnota | Pouzdro | LCSC |")
        out.append("| --- | --- | --- | --- |")
        for r in refs:
            c = comps[r]
            out.append(f"| {r} | {c['value']} | {c['fp']} | {c['lcsc'] or '—'} |")
    tables["kusovnik"] = "\n".join(out)

    # H743 pin map
    out = ["| Kulička | Pin | Síť | Funkce (hwdef Pavo20AIO) | Kam vede |", "| --- | --- | --- | --- | --- |"]
    rows = []
    for ball, (net, func) in pins["U301"].items():
        pin = func.rsplit("_", 1)[0]
        s = short(net)
        if s.startswith("unconnected"):
            s, goes = "—", "nezapojeno"
        else:
            others = sorted({r for r in nets[net] if r != "U301"}, key=key)
            if len(others) > 12:
                goes = f"napájecí síť ({len(others)} dílů)"
            else:
                goes = ", ".join(others) if others else "jen štítek, čeká na zapojení"
        rows.append((pin, ball, s, FUNCTION.get(s, ""), goes))
    order = lambda r: (r[0][:2] if r[0].startswith("P") else "~", int(re.sub(r"\D", "", r[0][2:]) or 0), r[0])
    for pin, ball, s, f, goes in sorted(rows, key=order):
        out.append(f"| {ball} | {pin} | {s} | {f} | {goes} |")
    tables["piny"] = "\n".join(out)

    # nets crossing sheets
    out = ["| Síť | Listy | Součástky |", "| --- | --- | --- |"]
    for name, refs in sorted(nets.items(), key=lambda kv: short(kv[0])):
        sheets = sorted({comps[r]["sheet"] for r in refs})
        if len(sheets) > 1 and short(name) not in ("GND",):
            rs = sorted(set(refs), key=key)
            shown = ", ".join(rs[:10]) + (f" … (+{len(rs) - 10})" if len(rs) > 10 else "")
            out.append(f"| {short(name)} | {', '.join(sheets)} | {shown} |")
    tables["site"] = "\n".join(out)

    doc = open(DOC).read()
    for k, v in tables.items():
        doc, n = re.subn(rf"(<!-- tabulky:{k} -->).*?(<!-- /tabulky:{k} -->)",
                         lambda m: f"{m.group(1)}\n{v}\n{m.group(2)}", doc, flags=re.S)
        assert n == 1, k
    open(DOC, "w").write(doc)
    print("NAVRH.md: tabulky", ", ".join(tables))


if __name__ == "__main__":
    main()
